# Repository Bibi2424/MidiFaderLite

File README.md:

# MidiFaderLite

Mini Midi controller with moving fader

## Hardware

TBD

## ID

TBD

## Firmware

### USB MIDI Name

 _Note_: 

 to change the midi device name of teensy32, you need to find the usb_desc.h file (located _platformio_/packages/framework-arduinoteensy/cores/teensy3/usbdesc.h)

 Locate the section that match the USB device type (USB_MIDI or USB_MIDI_SERIAL) and change the __PRODUCT_NAME__, __PRODUCT_NAME_LEN__ but also __VENDOR_ID__ and __PRODUCT_ID__

 ```c

#elif defined(USB_MIDI_SERIAL)
  // #define VENDOR_ID		0x16C0
  // #define PRODUCT_ID		0x0489
  #define VENDOR_ID   0xF6C0
  #define PRODUCT_ID    0xF489
  #define MANUFACTURER_NAME	{'T','e','e','n','s','y','d','u','i','n','o'}
  #define MANUFACTURER_NAME_LEN	11
  // #define PRODUCT_NAME		{'T','e','e','n','s','y',' ','M','I','D','I'}
  // #define PRODUCT_NAME_LEN	11
  #define PRODUCT_NAME    {'M','i','d','i','F','a','d','e','r','L','i','t','e'}
  #define PRODUCT_NAME_LEN  13
 ...
 ```

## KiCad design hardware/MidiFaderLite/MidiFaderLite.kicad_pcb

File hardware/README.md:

# MidiFaderLite Hardware

 - Made with KiCad v5.1
 - Schematic for reference only, the prototype was made on protoboard.

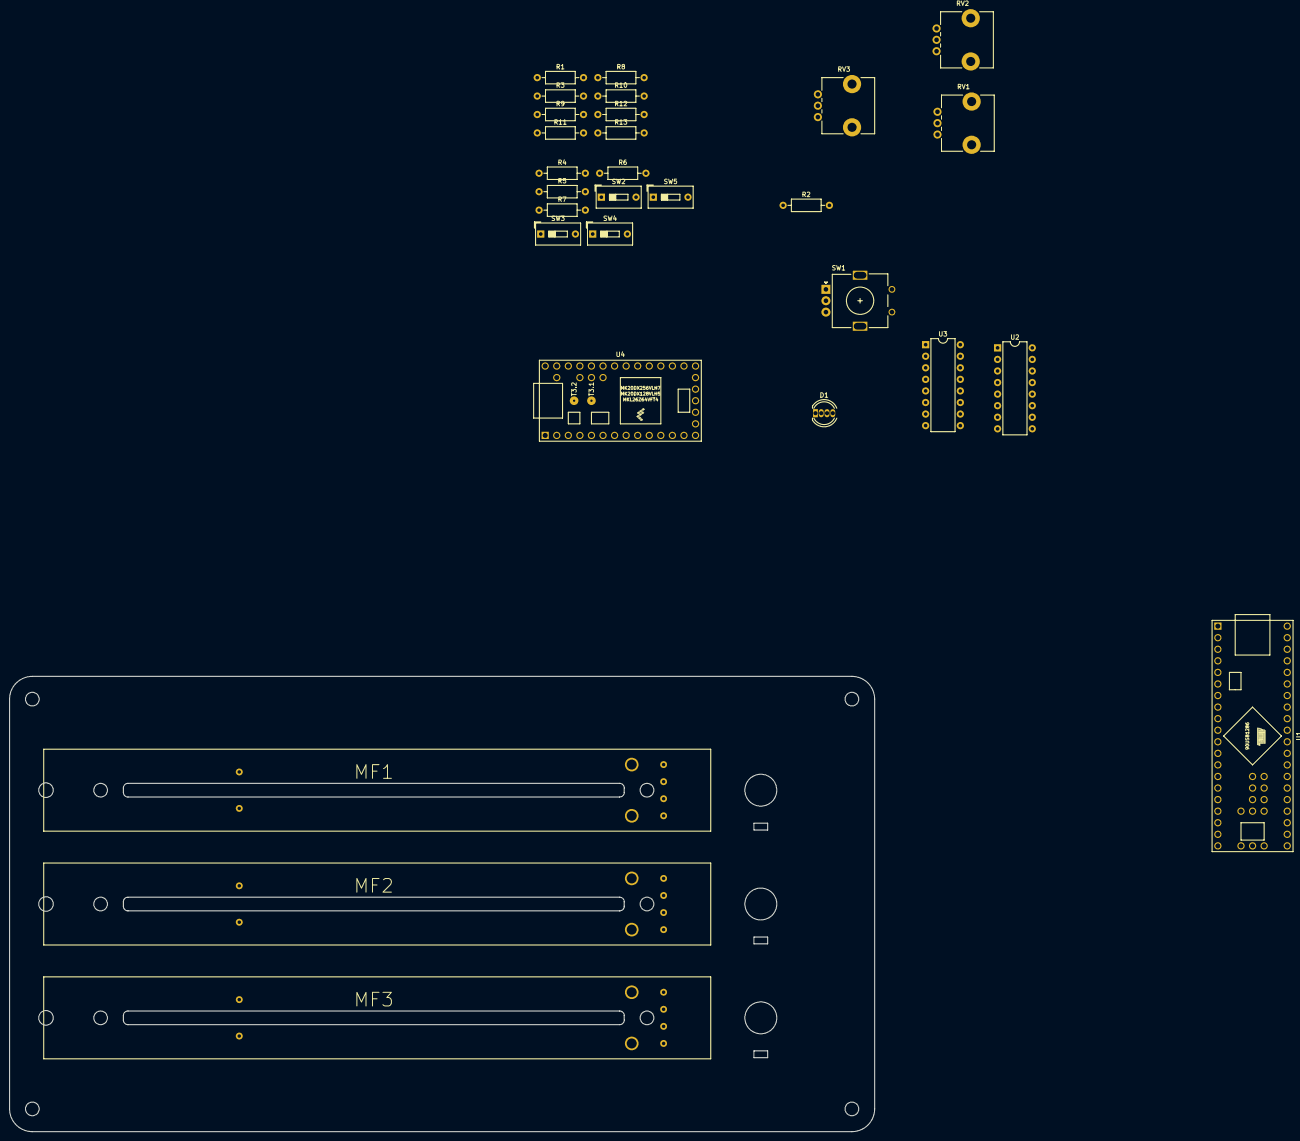
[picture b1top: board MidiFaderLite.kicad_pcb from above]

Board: 2 copper layers, 190.0 x 100.0 mm, 29 parts (0 on the bottom side), 43 nets, no tracks yet.

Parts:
D1: LED_CRGB; LED_D5.0mm-4_RGB
MF1, MF2, MF3: MFader
R1, R2, R3, R4, R5, R6, R7, R8, R9, R10, R11, R12, R13: R_Small; R_Axial_DIN0207_L6.3mm_D2.5mm_P10.16mm_Horizontal
RV1, RV2, RV3: R_POT; Potentiometer_Alps_RK09L_Single_Vertical
SW1: Rotary_Encoder; RotaryEncoder_Alps_EC11E_Vertical_H20mm
SW2, SW3, SW4, SW5: SW_SPST; SW_DIP_SPSTx01_Slide_9.78x4.72mm_W7.62mm_P2.54mm
U1: Teensy++2.0_(Arduino); Teensy2.0++
U2, U3: L293D; DIP-16_W7.62mm
U4: Teensy3.2; Teensy30_31_32_LC

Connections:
+3V3: U4.16, U4.31
+5V: MF1.3, MF2.3, MF3.3, R1.2, R2.2, R4.1, R5.1, R6.1, R7.1, R12.2, RV1.3, RV2.3, RV3.3, U1.21, U1.43, U2.16, U3.16, U4.34
Button1: R4.2, SW2.2, U1.36, U4.2
Button2: R5.2, SW3.2, U1.37, U4.3
Button3: R6.2, SW4.2, U1.38, U4.4
Button4: R7.2, SW5.2, U1.39, U4.5
DIRAFadeur1: U1.11, U2.2, U4.9
DIRAFadeur2: U1.13, U2.10, U4.13
DIRAFadeur3: U1.15, U3.2, U4.6
DIRBFadeur1: U1.12, U2.7, U4.10
DIRBFadeur2: U1.14, U2.15, U4.14
DIRBFadeur3: U1.16, U3.7, U4.7
GNDREF: D1.1, MF1.1, MF2.1, MF3.1, RV1.1, RV2.1, RV3.1, SW1.C, SW2.1, SW3.1, SW4.1, SW5.1, U1.1, U1.22, U1.33, U2.4, U2.5, U2.12, U2.13, U3.4, U3.5, U3.12, U3.13, U4.1, U4.17, U4.32
LED_BLUE: R9.2, U1.40, U4.30
LED_GREEN: R10.2, U1.41, U4.29
LED_RED: R11.2, U1.42, U4.28
unnamed: D1.2, R11.1
unnamed: D1.3, R10.1
unnamed: D1.4, R9.1
unnamed: MF1.4, U2.3
unnamed: MF1.5, U2.6
unnamed: MF1.6, R1.1, R3.1
unnamed: MF2.4, U3.3
unnamed: MF2.5, U3.6
unnamed: MF2.6, R2.1, R8.1
unnamed: MF3.4, U2.11
unnamed: MF3.5, U2.14
unnamed: MF3.6, R12.1, R13.1
POT1: RV1.2, U1.24, U4.21
POT2: RV3.2, U1.25, U4.22
POT3: RV2.2, U1.26, U4.23
ROTA: SW1.A, U1.3, U4.36
ROTB: SW1.B, U1.4, U4.37
Slider1: MF1.2, U1.31
Slider2: MF3.2, U1.30
Slider3: MF2.2, U1.29
SpeedFadeur1: U1.17, U2.1, U4.11
SpeedFadeur2: U1.18, U2.9, U4.12
SpeedFadeur3: U1.19, U3.1, U4.8
Touch1: R3.2, U1.44, U4.24
Touch2: R13.2, U1.45, U4.25
Touch3: R8.2, U1.46, U4.26
VCC: U2.8, U3.8

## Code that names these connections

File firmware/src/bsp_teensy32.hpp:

#ifndef BSP_TEENSY32_H
#define BSP_TEENSY32_H

#include <stdint.h>
#include <ADC.h>

#define LED_RED             4
#define LED_GREEN           5
#define LED_BLUE            6

#define FADER1_DIR_A_PIN    2
#define FADER1_DIR_B_PIN    1
#define FADER1_SPEED_PIN    3
#define FADER1_TOUCH_PIN    15
#define FADER1_POT_PIN      A0

#define FADER2_DIR_A_PIN    7
#define FADER2_DIR_B_PIN    8
#define FADER2_SPEED_PIN    9
#define FADER2_TOUCH_PIN    17
#define FADER2_POT_PIN      A2

#define FADER3_DIR_A_PIN    12
#define FADER3_DIR_B_PIN    11
#define FADER3_SPEED_PIN    10
#define FADER3_TOUCH_PIN    19
#define FADER3_POT_PIN      A4

#define POT1_PIN            A11
#define POT2_PIN            A10
#define POT3_PIN            A9

#define ENCODER1_PIN_A      20
#define ENCODER1_PIN_B      21

#define ENCODER2_PIN_A      0
#define ENCODER2_PIN_B      22

#define BUTTON1_PIN         25
#define BUTTON2_PIN         26
#define BUTTON3_PIN         27
#define BUTTON4_PIN         28
#define BUTTON5_PIN         29
#define BUTTON6_PIN         30
#define BUTTON7_PIN         31
#define BUTTON8_PIN         32

#define RESOLUTION_MAX_VALUE    1023

#define USE_HW_TOUCH            true

//! FIXME: Ugly as hell, I got nothing better at the moment
#define DECLARE_ADC    ADC adc;
extern ADC adc;

static inline void init_adc(void) {
    adc.adc0->setAveraging(32);
    adc.adc0->setResolution(10);
    adc.adc0->setConversionSpeed(ADC_CONVERSION_SPEED::MED_SPEED);
    adc.adc0->setSamplingSpeed(ADC_SAMPLING_SPEED::MED_SPEED);
}

static inline uint16_t adc_get(int pin) {
    return adc.adc0->analogRead(pin);
}

static inline void init_all_pins(void) {
    pinMode(FADER1_DIR_A_PIN, OUTPUT);
    pinMode(FADER1_DIR_B_PIN, OUTPUT);
    pinMode(FADER1_SPEED_PIN, OUTPUT);
    pinMode(FADER1_POT_PIN, INPUT);
    pinMode(FADER2_DIR_A_PIN, OUTPUT);
    pinMode(FADER2_DIR_B_PIN, OUTPUT);
    pinMode(FADER2_SPEED_PIN, OUTPUT);
    pinMode(FADER2_POT_PIN, INPUT);
    pinMode(FADER3_DIR_A_PIN, OUTPUT);
    pinMode(FADER3_DIR_B_PIN, OUTPUT);
    pinMode(FADER3_SPEED_PIN, OUTPUT);
    pinMode(FADER3_POT_PIN, INPUT);

    pinMode(POT1_PIN, INPUT);
    pinMode(POT2_PIN, INPUT);
    pinMode(POT3_PIN, INPUT);

    pinMode(LED_RED, OUTPUT);
    pinMode(LED_GREEN, OUTPUT);
    pinMode(LED_BLUE, OUTPUT);
}

static inline void init_pwm(void) {
    analogWriteFrequency(FADER1_SPEED_PIN, 20000);
    analogWriteFrequency(FADER2_SPEED_PIN, 20000);
    analogWriteFrequency(FADER3_SPEED_PIN, 20000);
    analogWriteResolution(10);
}
static inline void set_pwm(int pin, uint16_t value) { analogWrite(pin, value); }

#endif

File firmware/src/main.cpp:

#include <Arduino.h>
#include <stdint.h>
#include <MIDI.h>
#define ENCODER_OPTIMIZE_INTERRUPTS
#include <Encoder.h>

#include "global.hpp"
#include "bsp.hpp"
#include "fader.hpp"
#include "touch.hpp"
#include "encoder.hpp"
#include "potentiometer.hpp"
#include "button.hpp"
#include "light_effect.hpp"


fader_t fader1 = {
    .dir_A_pin = FADER1_DIR_A_PIN,
    .dir_B_pin = FADER1_DIR_B_PIN,
    .speed_pin = FADER1_SPEED_PIN,
    .touch_pin = FADER1_TOUCH_PIN,
    .analog_pin = FADER1_POT_PIN,
    .m_deadzone = 625,

    .midi_control = 1,

    .analog_min_value = 0,
    .analog_max_value = 1023,
};
fader_t fader2 = {
    .dir_A_pin = FADER2_DIR_A_PIN,
    .dir_B_pin = FADER2_DIR_B_PIN,
    .speed_pin = FADER2_SPEED_PIN,
    .touch_pin = FADER2_TOUCH_PIN,
    .analog_pin = FADER2_POT_PIN,
    .m_deadzone = 750,

    .midi_control = 7,

    .analog_min_value = 0,
    .analog_max_value = 1023,
};
fader_t fader3 = {
    .dir_A_pin = FADER3_DIR_A_PIN,
    .dir_B_pin = FADER3_DIR_B_PIN,
    .speed_pin = FADER3_SPEED_PIN,
    .touch_pin = FADER3_TOUCH_PIN,
    .analog_pin = FADER3_POT_PIN,
    .m_deadzone = 625,

    .midi_control = 11,

    .analog_min_value = 0,
    .analog_max_value = 1023,
};

potentiometer_t pot1 = {
    .analog_pin = POT1_PIN,
    .midi_control = 0x10
};
potentiometer_t pot2 = {
    .analog_pin = POT2_PIN,
    .midi_control = 0x11
};
potentiometer_t pot3 = {
    .analog_pin = POT3_PIN,
    .midi_control = 0x12
};

Encoder enc1(ENCODER1_PIN_A, ENCODER1_PIN_B);
encoder_t encoder1 = {
    .object = enc1,
    .midi_control = 0x13,
};
Encoder enc2(ENCODER2_PIN_A, ENCODER2_PIN_B);
encoder_t encoder2 = {
    .object = enc2,
    .midi_control = 0x14,
};

button_t b1 = { .pin = 25, .midi_control = 0x18 };
button_t b2 = { .pin = 26, .midi_control = 0x19 };
button_t b3 = { .pin = 27, .midi_control = 0x1A };
button_t b4 = { .pin = 28, .midi_control = 0x1B };
button_t b5 = { .pin = 29, .midi_control = 0x1C };
button_t b6 = { .pin = 30, .midi_control = 0x1D };
button_t b7 = { .pin = 31, .midi_control = 0x1E };
button_t b8 = { .pin = 32, .midi_control = 0x1F };

DECLARE_ADC;


void myControlChange(byte channel, byte control, byte value) {
    // Serial.printf("IN[%u-%u]: %u\n", channel, control, value);
    if(channel != 1) { return; }

    light_effect_register_event((event_type_t){.midi_rx = 1});

    if(fader1.midi_control == control) {
        // Serial.printf("IN:%u\n", value);
        fader_set(fader1, value);
    }
    if(fader2.midi_control == control) {
        // Serial.printf("IN:%u\n", value);
        fader_set(fader2, value);
    }
    if(fader3.midi_control == control) {
        // Serial.printf("IN:%u\n", value);
        fader_set(fader3, value);
    }
}


void setup(void) {
    asm(".global _printf_float");

    // initialize LED digital pin as an output.
    pinMode(LED_BUILTIN, OUTPUT);
    Serial.begin(115200);

    init_adc();
    init_all_pins();
    init_pwm();
    init_touch();

    light_effect_init();

    fader_init(fader1);
    fader_init(fader2);
    fader_init(fader3);

    potentiometer_init(pot1);
    potentiometer_init(pot2);
    potentiometer_init(pot3);

    button_init(b1);
    button_init(b2);
    button_init(b3);
    button_init(b4);
    button_init(b5);
    button_init(b6);
    button_init(b7);
    button_init(b8);

    usbMIDI.setHandleControlChange(myControlChange);

    Serial.println("Init Done");
}


void loop(void) {
    long current_time = millis();
    bool midi_tx_event = false;

#if 1
    usbMIDI.read();
#endif

#if 1
    static long fader_last_process_time = 0;
    static long fader_last_send_time = 0;

    if(current_time - fader_last_process_time > 5) {

        fader_process(fader1);
        fader_process(fader2);
        fader_process(fader3);
        fader_last_process_time = current_time;
    }

#endif

#if 1
    static long pots_last_run_time = 0;

    if(current_time - pots_last_run_time > 50) {
        potentiometer_get(pot1);
        potentiometer_get(pot2);
        potentiometer_get(pot3);

        pots_last_run_time = current_time;
    }
#endif

#if 1
    static long encs_last_process_time = 0;

    if(current_time - encs_last_process_time > 5) {
        encoder_get(encoder1);
        encoder_get(encoder2);

        encs_last_process_time = current_time;
    }
#endif

#if 1
    if(current_time - fader_last_send_time > 25) {
        midi_tx_event |= fader_send(fader1, false);
        midi_tx_event |= fader_send(fader2, false);
        midi_tx_event |= fader_send(fader3, false);
        midi_tx_event |= potentiometer_send(pot1, false);
        midi_tx_event |= potentiometer_send(pot2, false);
        midi_tx_event |= potentiometer_send(pot3, false);
        midi_tx_event |= encoder_send(encoder1);
        midi_tx_event |= encoder_send(encoder2);
        fader_last_send_time = current_time;
    }
#endif

#if 1
    static long button_last_process_time = 0;
    if(current_time - button_last_process_time > 1) {
        if(button_update(b1)) {
            midi_tx_event |= button_send(b1);
        }
        if(button_update(b2)) {
            midi_tx_event |= button_send(b2);
        }
        if(button_update(b3)) {
            midi_tx_event |= button_send(b3);
        }
        if(button_update(b4)) {
            midi_tx_event |= button_send(b4);
        }
        if(button_update(b5)) {
            midi_tx_event |= button_send(b5);
        }
        if(button_update(b6)) {
            midi_tx_event |= button_send(b6);
        }
        if(button_update(b7)) {
            midi_tx_event |= button_send(b7);
        }
        if(button_update(b8)) {
            midi_tx_event |= button_send(b8);
        }
        button_last_process_time = current_time;
    }
#endif

if(midi_tx_event) {
    light_effect_register_event((event_type_t){.midi_tx = 1});
}

#if 1
    light_effect_run();
#endif

#if 0
    static long touch_last_run_time = 0;
    //! NOTE: Usefull to verify the capacitve touch
    if(current_time - touch_last_run_time > 100) {
        long touch1 = get_touch(FADER1_TOUCH_PIN);
        long touch2 = get_touch(FADER2_TOUCH_PIN);
        long touch3 = get_touch(FADER3_TOUCH_PIN);
        Serial.printf("Touch: %u %u %u\n", touch1, touch2, touch3);
    }
#endif

#if 0
    //! NOTE: Usefull to verify the slide faders
    int slide1 = analogRead(FADER1_POT_PIN);
    int slide2 = analogRead(FADER2_POT_PIN);
    int slide3 = analogRead(FADER3_POT_PIN);
    Serial.printf("Slider: %u %u %u\n", slide1, slide2, slide3);

    delay(100);
#endif

#if 0
    //! NOTE: Usefull to discover the OUTPUT_DEAD_ZONE

    int target = analogRead(A0);
    // target = map(target, 0, 1023, -1023, 1023);
    target = (target * 2) - 1023;
    if(target > 0 && target < 20) { target = 0; }
    if(target < 0 && target > -20) { target = 0; }
    set_motor_speed(target);

    Serial.print("Target: ");
    Serial.println(target);

    delay(20);

#endif
}

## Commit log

2021-10-21 Basic structure in place, placeholder firmawre for the moment
2021-10-25 Abstract fader control, add bsp for different boards
2021-10-25 Update schematic with latest plan
2021-10-26 abstract fader touch (ugly but works)
2021-10-27 First working loop with the DAW
2021-11-01 Update touch with main file test and works with teensy32
2021-11-06 Update teensy32 bsp, start expending for proto controller
2021-11-06 Add proper handling for pots
2021-11-07 Add encoder, improve fader
2021-11-07 Add really basic button support
2021-11-08 Update some MIDI timings
2021-11-20 Update device map
2021-12-11 Improve Fader stability, remobe touch from midi mapping
2021-12-11 Update buttons with Bounce2
2021-12-11 Fix bug where speed was not set to 0 on touch, tweaks to the asserv
2021-12-12 Improve ADC readings (still needs to abstract it)
2021-12-12 Abstract the new ADC sampling (ugly for now)
2021-12-12 Tweaking faders and encoders
2021-12-12 Add README to Map folder to explain where to put the files
2021-12-28 Add really basic light effect, slow some process to prevent USB bug
2021-12-29 Add integral to fader, move deadzone per device
2022-01-03 Changes around light effects and events
2022-01-03 Update Map, to use encoders as zoom and scroll by default
2022-01-03 Update schematics, remove other hardware related files
2022-01-03 Add step files of the assembly, add 3mf for printed parts
2022-01-03 Add some images
